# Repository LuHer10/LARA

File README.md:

# LARA (Low-cost Assistive Robot Arm)
Repositorio Trabajo Fin de Grado

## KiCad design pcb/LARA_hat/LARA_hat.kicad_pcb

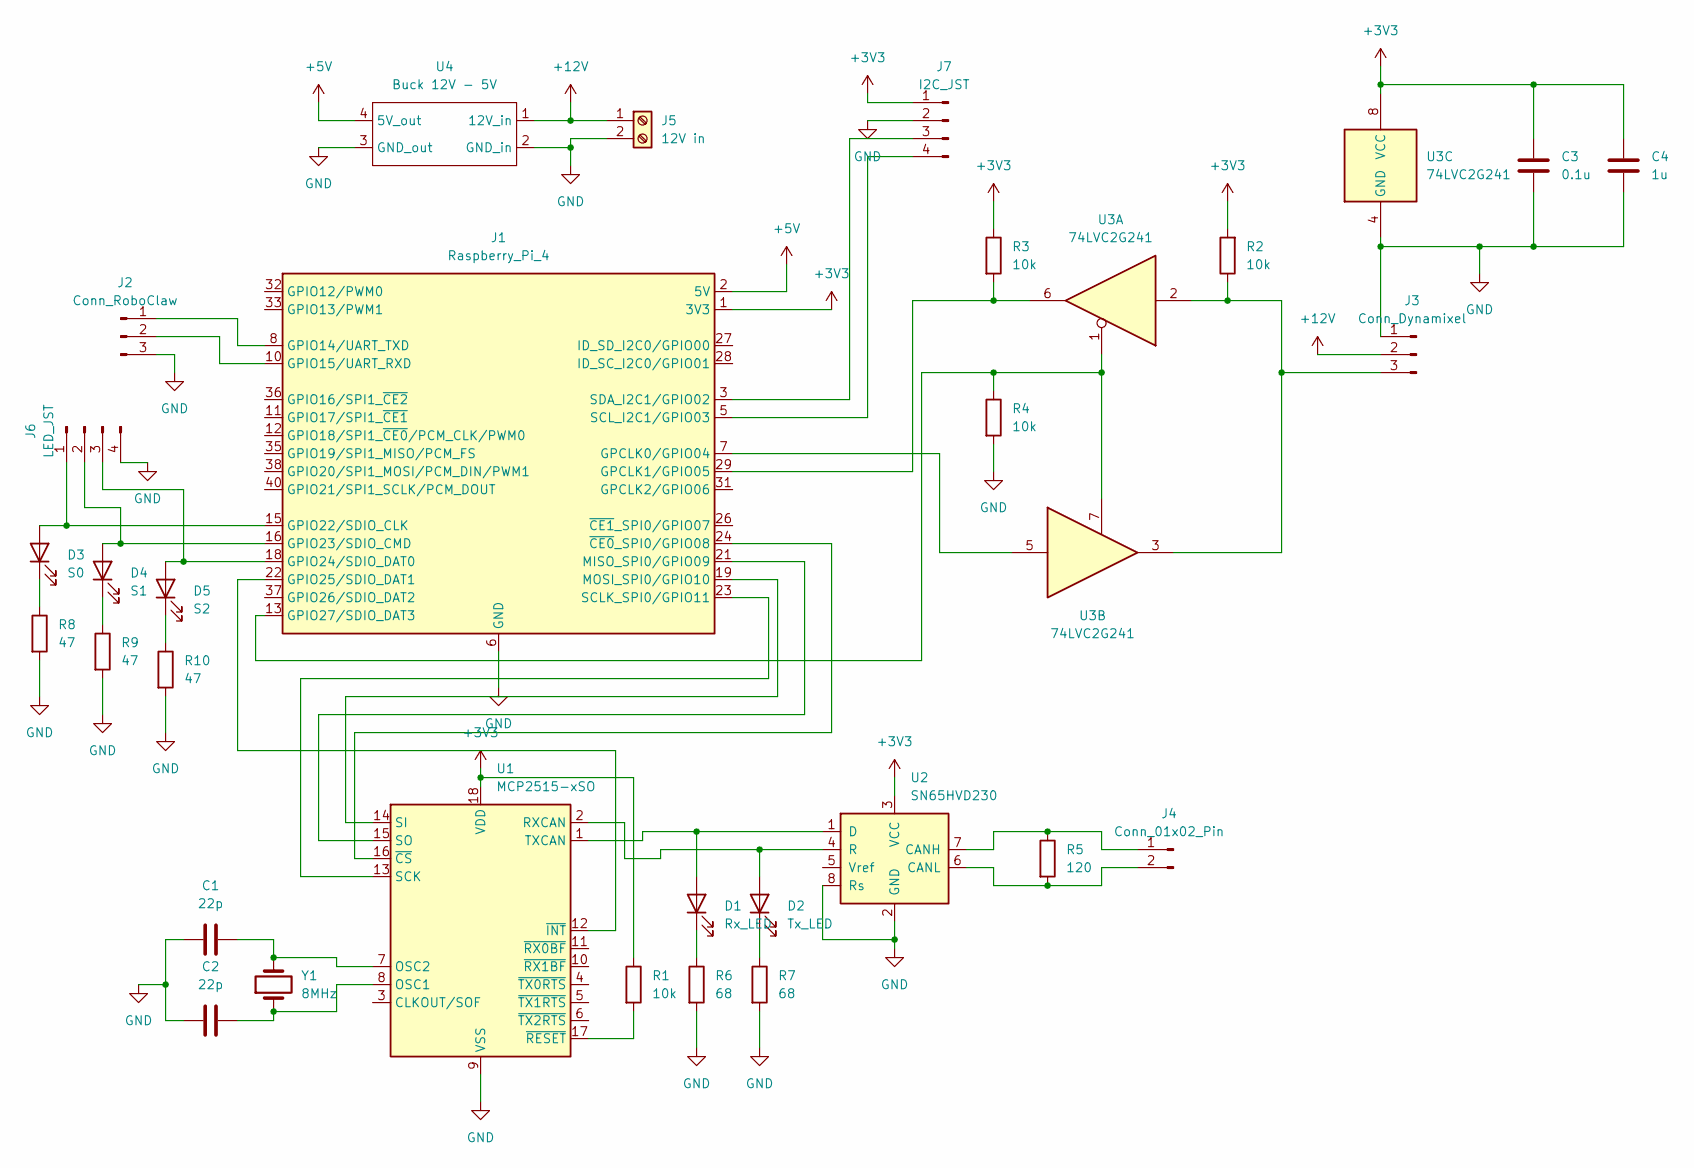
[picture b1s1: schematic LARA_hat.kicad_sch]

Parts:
C1, C2: 22p; C_0805_2012Metric_Pad1.18x1.45mm_HandSolder
C3: 0.1u; C_0805_2012Metric_Pad1.18x1.45mm_HandSolder
C4: 1u; C_0805_2012Metric_Pad1.18x1.45mm_HandSolder
D1: Rx_LED; LED_0805_2012Metric_Pad1.15x1.40mm_HandSolder
D2: Tx_LED; LED_0805_2012Metric_Pad1.15x1.40mm_HandSolder
D3: S0; LED_0805_2012Metric_Pad1.15x1.40mm_HandSolder
D4: S1; LED_0805_2012Metric_Pad1.15x1.40mm_HandSolder
D5: S2; LED_0805_2012Metric_Pad1.15x1.40mm_HandSolder
J1: Raspberry_Pi_4; PinHeader_2x20_P2.54mm_Vertical
J2: Conn_RoboClaw; JST_PH_B3B-PH-K_1x03_P2.00mm_Vertical
J3: Conn_Dynamixel; JST_EH_B3B-EH-A_1x03_P2.50mm_Vertical
J4: Conn_01x02_Pin; JST_PH_B2B-PH-K_1x02_P2.00mm_Vertical
J5: 12V in; TerminalBlock_MaiXu_MX126-5.0-02P_1x02_P5.00mm
J6: LED_JST; JST_PH_B4B-PH-K_1x04_P2.00mm_Vertical
J7: I2C_JST; JST_PH_B4B-PH-K_1x04_P2.00mm_Vertical
R1, R2, R3, R4: 10k; R_0805_2012Metric_Pad1.20x1.40mm_HandSolder
R5: 120; R_0805_2012Metric_Pad1.20x1.40mm_HandSolder
R6, R7: 68; R_0805_2012Metric_Pad1.20x1.40mm_HandSolder
R8, R9, R10: 47; R_0805_2012Metric_Pad1.20x1.40mm_HandSolder
U1: MCP2515-xSO; SOIC-18W_7.5x11.6mm_P1.27mm
U2: SN65HVD230; SOIC-8_3.9x4.9mm_P1.27mm
U3: 74LVC2G241; VSSOP-8_3x3mm_P0.65mm
U4: Buck 12V - 5V; BUCK12-5
Y1: 8MHz; Crystal_HC49-4H_Vertical

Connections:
+3V3: C3.1, C4.1, J1.1 (3V3), J1.17 (3V3), J7.1, R1.1, R2.2, R3.1, U1.18 (VDD), U2.3 (VCC), U3.8 (VCC)
+5V: J1.2 (5V), J1.4 (5V), U4.4 (5V_out)
+12V: J3.2, J5.1, U4.1 (12V_in)
GND: C1.1, C2.1, C3.2, C4.2, J1.6 (GND), J1.9 (GND), J1.14 (GND), J1.20 (GND), J1.25 (GND), J1.30 (GND), J1.34 (GND), J1.39 (GND), J2.3, J3.1, J5.2, J6.4, J7.2, R4.2, R6.2, R7.2, R8.2, R9.2, R10.2, U1.9 (VSS), U2.2 (GND), U2.8 (Rs), U3.4 (GND), U4.2 (GND_in), U4.3 (GND_out)
unnamed: D1.2 (A), U1.1 (TXCAN), U2.1 (D)
unnamed: D1.1 (K), R6.1
unnamed: D2.2 (A), U1.2 (RXCAN), U2.4 (R)
unnamed: D2.1 (K), R7.1
unnamed: D3.2 (A), J1.15 (GPIO22/SDIO_CLK), J6.1
unnamed: D3.1 (K), R8.1
unnamed: D4.2 (A), J1.16 (GPIO23/SDIO_CMD), J6.2
unnamed: D4.1 (K), R9.1
unnamed: D5.2 (A), J1.18 (GPIO24/SDIO_DAT0), J6.3
unnamed: D5.1 (K), R10.1
unnamed: J1.7 (GPCLK0/GPIO04), U3.5
unnamed: J1.29 (GPCLK1/GPIO05), R3.2, U3.6
unnamed: J1.8 (GPIO14/UART_TXD), J2.1
unnamed: J1.10 (GPIO15/UART_RXD), J2.2
unnamed: J1.22 (GPIO25/SDIO_DAT1), U1.12 (~INT)
unnamed: J1.13 (GPIO27/SDIO_DAT3), R4.1, U3.1, U3.7
unnamed: J1.21 (MISO_SPI0/GPIO09), U1.15 (SO)
unnamed: J1.19 (MOSI_SPI0/GPIO10), U1.14 (SI)
unnamed: J1.23 (SCLK_SPI0/GPIO11), U1.13 (SCK)
unnamed: J1.5 (SCL_I2C1/GPIO03), J7.4
unnamed: J1.3 (SDA_I2C1/GPIO02), J7.3
unnamed: J1.24 (~CE0_SPI0/GPIO08), U1.16 (~CS)
unnamed: J3.3, R2.1, U3.2, U3.3
unnamed: J4.1, R5.1, U2.7 (CANH)
unnamed: J4.2, R5.2, U2.6 (CANL)
unnamed: C2.2, U1.8 (OSC1), Y1.1
unnamed: C1.2, U1.7 (OSC2), Y1.2
unnamed: R1.2, U1.17 (~RESET)

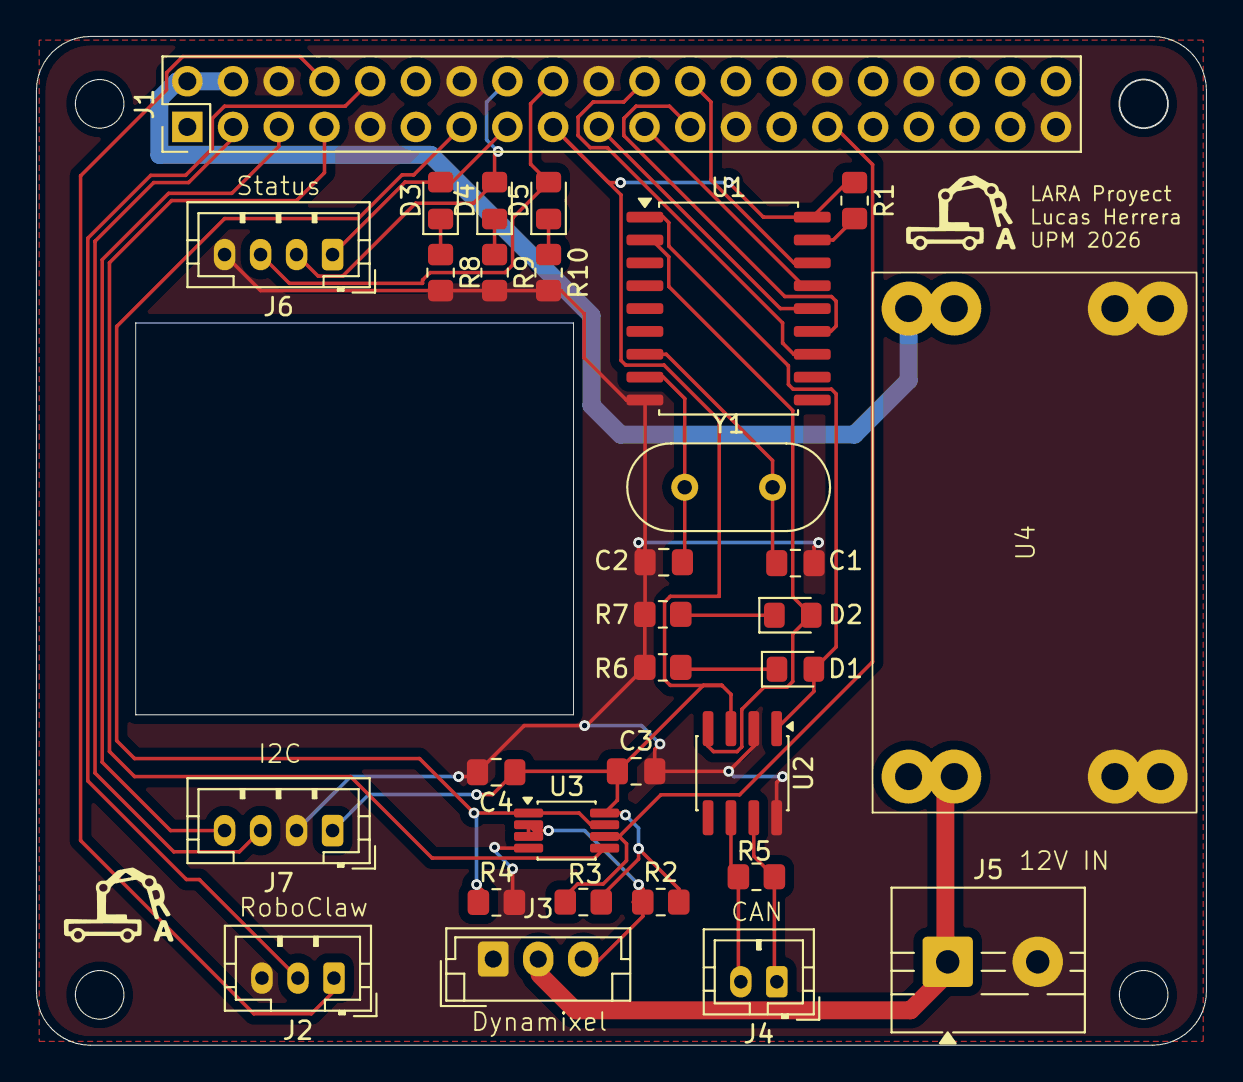
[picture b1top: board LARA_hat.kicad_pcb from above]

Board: 2 copper layers, 64.9 x 56.0 mm, 31 parts (0 on the bottom side), 32 nets.

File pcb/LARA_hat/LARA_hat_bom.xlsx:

Reference | Qty | Value | Footprint
C1,C2 | 2 | 22p | Capacitor_SMD:C_0805_2012
C3 | 1 | 0.1u | Capacitor_SMD:C_0805_2012
C4 | 1 | 1u | Capacitor_SMD:C_0805_2012
D1 | 1 | Rx_LED | LED_SMD:LED_0805_2012
D2 | 1 | Tx_LED | LED_SMD:LED_0805_2012
D3 | 1 | S0 | LED_SMD:LED_0805_2012
D4 | 1 | S1 | LED_SMD:LED_0805_2012
D5 | 1 | S2 | LED_SMD:LED_0805_2012
J1 | 1 | Raspberry_Pi_4 | Connector_PinSocket_2.54mm:PinSocket_2x20_P2.54mm_Vertical
J2 | 1 | Conn_RoboClaw | Connector_JST:JST_PH_B3B-PH-K_1x03_P2.00mm_Vertical
J3 | 1 | Conn_Dynamixel | Connector_JST:JST_EH_B3B-EH-A_1x03_P2.50mm_Vertical
J4 | 1 | Conn_01x02_Pin | Connector_JST:JST_PH_B2B-PH-K_1x02_P2.00mm_Vertical
J5 | 1 | 12V in | TerminalBlock:TerminalBlock_MaiXu_MX126-5.0-02P_1x02_P5.00mm
J6 | 1 | LED_JST | Connector_JST:JST_PH_B4B-PH-K_1x04_P2.00mm_Vertical
J7 | 1 | I2C_JST | Connector_JST:JST_PH_B4B-PH-K_1x04_P2.00mm_Vertical
R1,R2,R3,R4 | 4 | 10k | Resistor_SMD:R_0805_2012
R5 | 1 | 120 | Resistor_SMD:R_0805_2012
R6,R7,R8,R9,R10 | 5 | 68 | Resistor_SMD:R_0805_2012
U1 | 1 | MCP2515-xSO | Package_SO:SOIC-18W_7.5x11.6mm_P1.27mm
U2 | 1 | SN65HVD230 | Package_SO:SOIC-8_3.9x4.9mm_P1.27mm
U3 | 1 | 74LVC2G241 | Package_SO:VSSOP-8_3x3mm_P0.65mm
Y1 | 1 | 8MHz | Crystal:Crystal_HC49-4H_Vertical

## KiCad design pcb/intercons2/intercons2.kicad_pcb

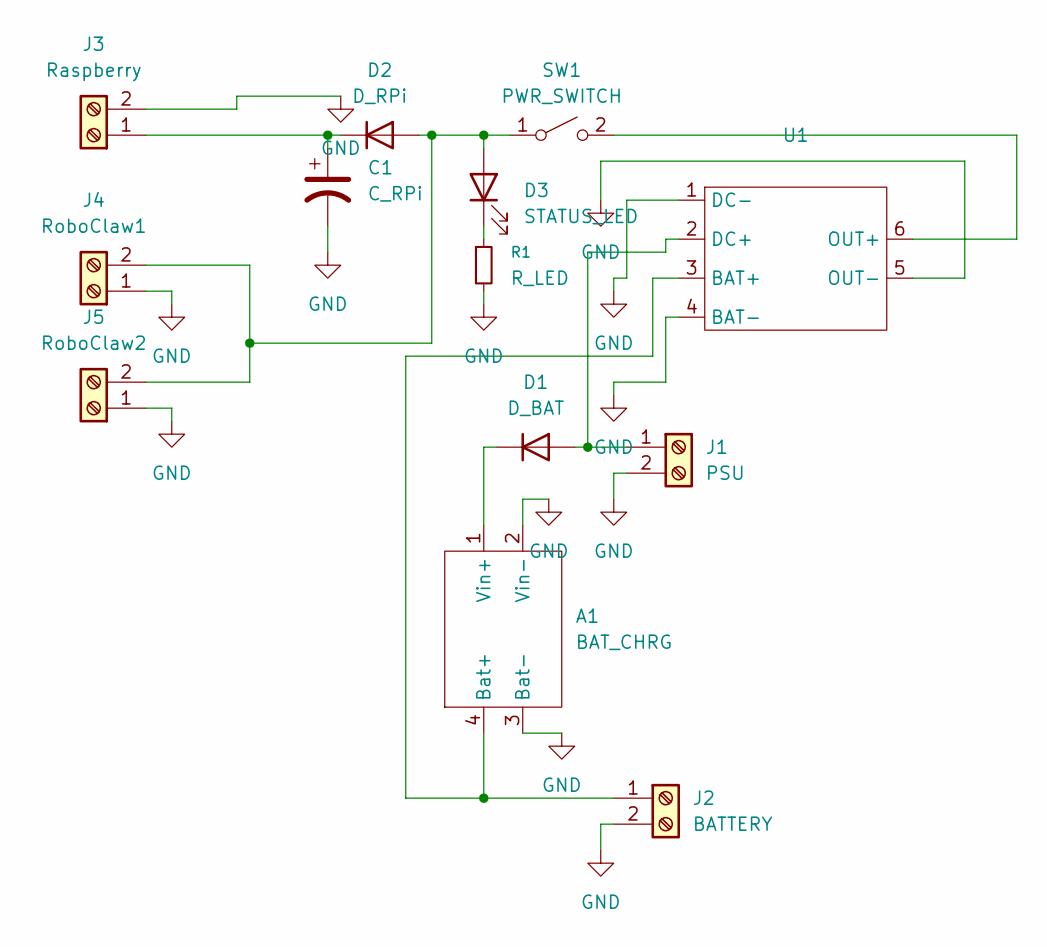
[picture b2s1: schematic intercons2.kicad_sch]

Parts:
A1: BAT_CHRG
C1: C_RPi; CP_Radial_D18.0mm_P7.50mm
D1: D_BAT; D_DO-27_P15.24mm_Horizontal
D2: D_RPi; D_DO-27_P15.24mm_Horizontal
D3: STATUS_LED; LED_D3.0mm
J1: PSU; TerminalBlock_MaiXu_MX126-5.0-02P_1x02_P5.00mm
J2: BATTERY; TerminalBlock_MaiXu_MX126-5.0-02P_1x02_P5.00mm
J3: Raspberry; TerminalBlock_MaiXu_MX126-5.0-02P_1x02_P5.00mm
J4: RoboClaw1; TerminalBlock_MaiXu_MX126-5.0-02P_1x02_P5.00mm
J5: RoboClaw2; TerminalBlock_MaiXu_MX126-5.0-02P_1x02_P5.00mm
R1: R_LED; R_Axial_DIN0204_L3.6mm_D1.6mm_P7.62mm_Horizontal
SW1: PWR_SWITCH; switch
U1: COMMUTER

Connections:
GND: A1.2 (Vin-), A1.3 (Bat-), C1.2, J1.2, J2.2, J3.2, J4.1, J5.1, R1.2, U1.1 (DC-), U1.4 (BAT-), U1.5 (OUT-)
unnamed: A1.4 (Bat+), J2.1, U1.3 (BAT+)
unnamed: A1.1 (Vin+), D1.1 (K)
unnamed: D1.2 (A), J1.1, U1.2 (DC+)
unnamed: D2.2 (A), D3.2 (A), J4.2, J5.2, SW1.1 (A)
unnamed: C1.1, D2.1 (K), J3.1
unnamed: D3.1 (K), R1.1
unnamed: SW1.2 (B), U1.6 (OUT+)

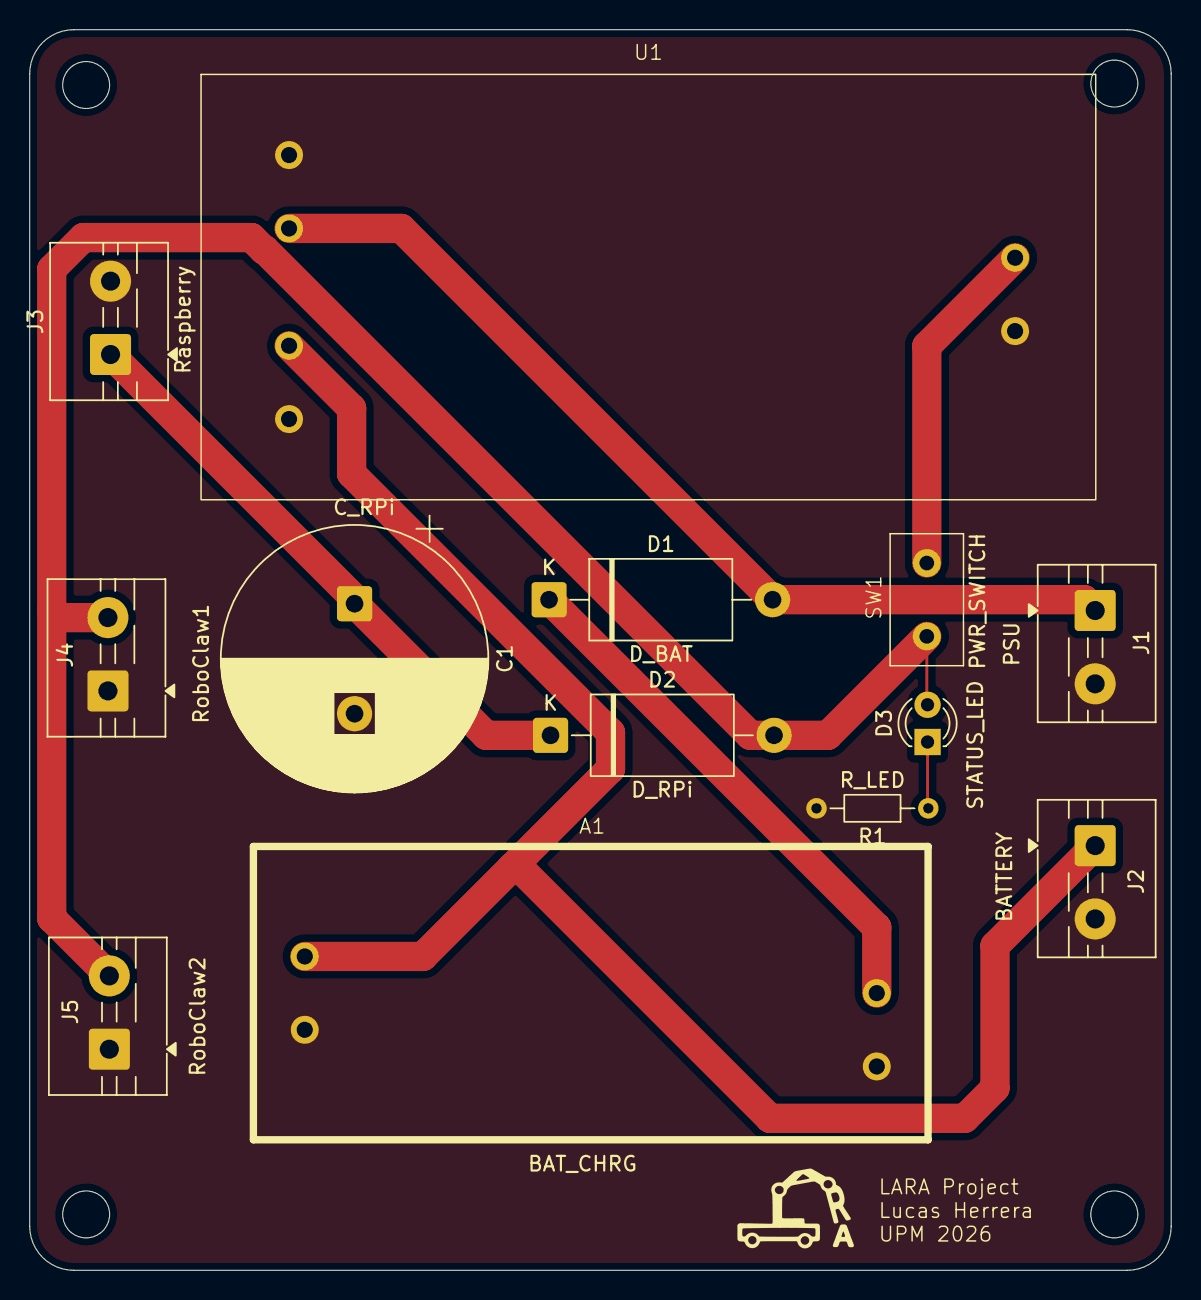
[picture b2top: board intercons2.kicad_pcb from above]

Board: 2 copper layers, 77.8 x 84.6 mm, 15 parts (1 on the bottom side), 8 nets.

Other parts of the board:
logo1, logo3: LOGO

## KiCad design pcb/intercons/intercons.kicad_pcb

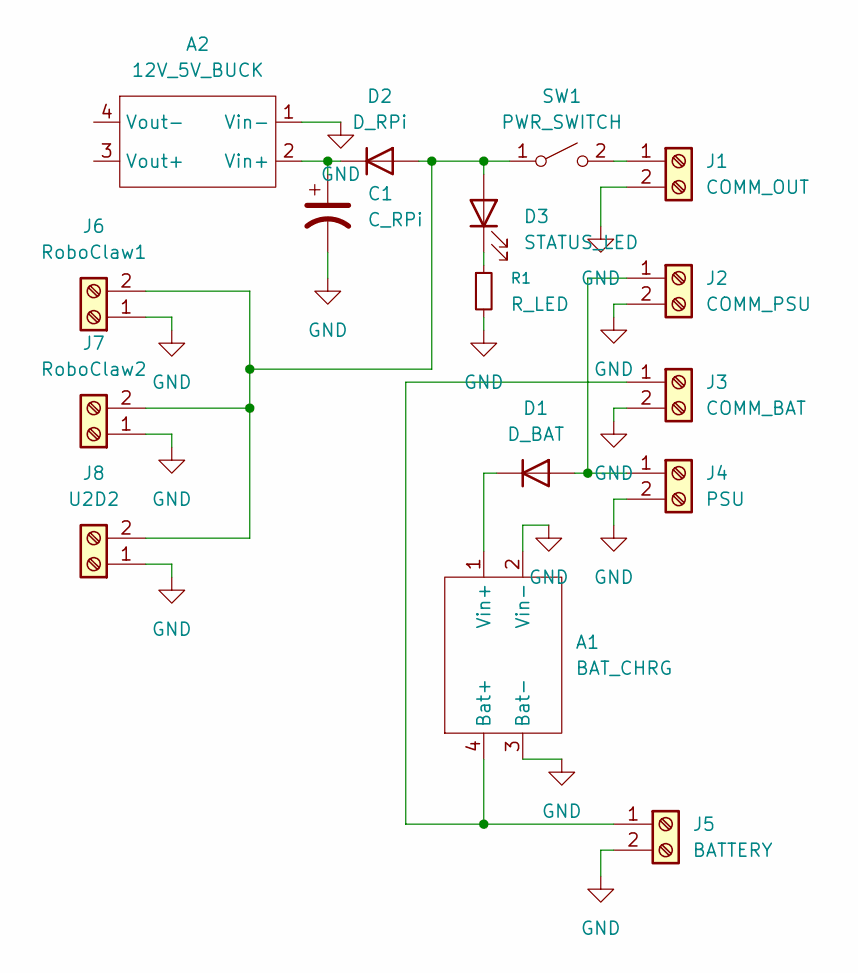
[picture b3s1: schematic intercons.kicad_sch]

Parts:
A1: BAT_CHRG
A2: 12V_5V_BUCK
C1: C_RPi; CP_Radial_D18.0mm_P7.50mm
D1: D_BAT; D_DO-27_P15.24mm_Horizontal
D2: D_RPi; D_DO-27_P15.24mm_Horizontal
D3: STATUS_LED; LED_D3.0mm
J1: COMM_OUT; TerminalBlock_MaiXu_MX126-5.0-02P_1x02_P5.00mm
J2: COMM_PSU; TerminalBlock_MaiXu_MX126-5.0-02P_1x02_P5.00mm
J3: COMM_BAT; TerminalBlock_MaiXu_MX126-5.0-02P_1x02_P5.00mm
J4: PSU; TerminalBlock_MaiXu_MX126-5.0-02P_1x02_P5.00mm
J5: BATTERY; TerminalBlock_MaiXu_MX126-5.0-02P_1x02_P5.00mm
J6: RoboClaw1; TerminalBlock_MaiXu_MX126-5.0-02P_1x02_P5.00mm
J7: RoboClaw2; TerminalBlock_MaiXu_MX126-5.0-02P_1x02_P5.00mm
J8: U2D2; TerminalBlock_MaiXu_MX126-5.0-02P_1x02_P5.00mm
R1: R_LED; R_Axial_DIN0204_L3.6mm_D1.6mm_P7.62mm_Horizontal
SW1: PWR_SWITCH; switch

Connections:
GND: A1.2 (Vin-), A1.3 (Bat-), A2.1 (Vin-), C1.2, J1.2, J2.2, J3.2, J4.2, J5.2, J6.1, J7.1, J8.1, R1.2
unnamed: A1.4 (Bat+), J3.1, J5.1
unnamed: A1.1 (Vin+), D1.1 (K)
unnamed: A2.2 (Vin+), C1.1, D2.1 (K)
unnamed: D1.2 (A), J2.1, J4.1
unnamed: D2.2 (A), D3.2 (A), J6.2, J7.2, J8.2, SW1.1 (A)
unnamed: D3.1 (K), R1.1
unnamed: J1.1, SW1.2 (B)

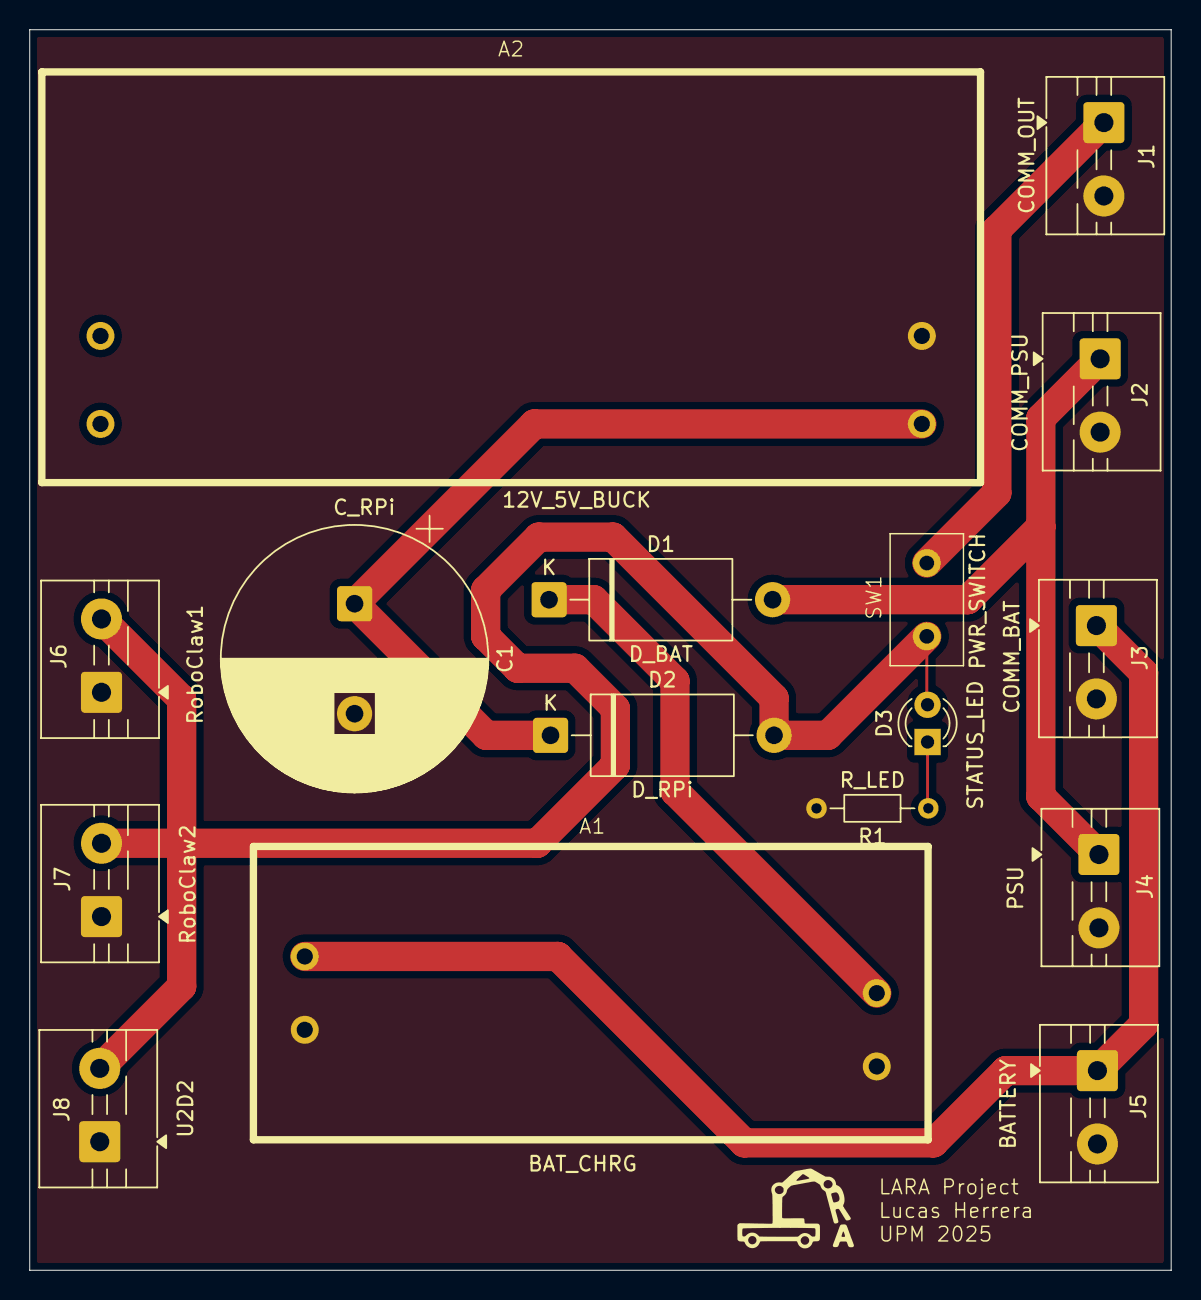
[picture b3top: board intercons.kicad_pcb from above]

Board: 2 copper layers, 77.8 x 84.6 mm, 18 parts (1 on the bottom side), 8 nets.

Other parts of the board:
logo1, logo3: LOGO

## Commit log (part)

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2025-06-08 test
2025-06-08 robot main.cpp added
2025-06-09 modified roboclaw_test program
2025-06-09 added Qt app code
2025-06-10 default RPi baud rate 115200
2025-06-13 added roboclaw.h to robot folder
2025-06-13 added roboclaw.cpp to robot folder
2025-06-13 modified main.cpp in robot to use roboclaw library
2025-06-13 new file structure
2025-06-14 added .gitignore
2025-06-14 added CMakelists.txt to robot
2025-06-14 CC BY-NC-SA 4.0 license
2025-06-15 updated .gitignore
2025-06-15 added functions for PWM and speed commands
2025-06-16 added encoder read method
2025-06-17 fixed error: bad file descriptor
2025-06-18 fixed encoder misread
2025-06-18 added encoder reset method
2025-06-18 added reaad speed method
2025-06-18 added base.h and base.cpp (Base class)
2025-06-19 added odometry functions to Base
2025-06-20 changed CMake structure
2025-06-20 changed test folder structure (CMake)
2025-06-23 Added destructor to base (stops the motors)
2025-06-23 added readSpeeds()
2025-06-23 added udp test program
2025-06-23 updated qt_app
2025-06-24 added test program for Base class
2025-06-24 updated CMakeLists.txt
2025-06-24 added test program for udp motor control
2025-06-24 fixed errors
2025-06-24 updated base.cpp
2025-06-24 updated udp_motor.cpp
2025-06-25 added new Network class
2025-06-25 added test program for network class
2025-06-25 updated base dimensions
2025-06-26 changed qt_app file structure
2025-06-26 added JoystickApp test project
2025-06-27 changed GUI in JoystickApp
2025-07-02 updated JoystickApp
2025-07-02 added designs folder
2025-07-07 added upper arm segments
2025-07-08 Updated servo placements for belts
2025-07-08 added gt2 belt calculator
2025-07-08 added pulley designs
2025-07-08 added pulley design
2025-07-15 changed pulleys to 25T - 50T
2025-07-15 updated pulleys
2025-07-15 new pulleys
2025-07-15 update AndroidManifest
2025-07-15 updated udp_motor_network.cpp
2025-07-22 changed belt lengths
2025-07-23 made holes for spacers
2025-07-23 24T and 48T pulleys
2025-07-24 improved message send/receive
2025-09-03 added arm assembly
2025-09-09 updated arm assembly
2025-09-16 dxf files added
2025-09-16 added new FCStd files
2025-09-17 updated pulley
2025-09-23 added bearing cover designs
2025-10-06 added spacers
2025-10-06 Updated external cover
2025-10-06 Updated covers
2025-10-17 updated gt2 48T pulley
2025-10-17 new covers
2025-10-21 changed server IP address
2025-10-23 updated/added parts
2025-10-23 increased inner diameter to 6mm
2025-10-27 added 0.2mm clearance
2025-10-28 pulleys optimized for printing
2025-10-28 spiky gt2 pulley generator
2025-10-30 added base designs
2025-11-14 added wrist
2025-11-14 fixed pulley
2025-11-14 new spacers
2025-11-14 pieces
2025-11-24 added KiCAD files
2025-11-28 new arm version
2025-12-01 added 6mm to servo slot
2025-12-02 added servo class
2025-12-02 added angle to position converter functions
2025-12-04 added operating mode functions
2025-12-04 fixed inverse kinematics error
2025-12-09 added arm attachment to base
2025-12-09 updated arm_base
2026-01-08 error fix
2026-01-08 added arm classs
2026-01-09 added grip button
2026-01-09 fixed error
2026-01-09 added out of reach detection
2026-01-09 arm test program
2026-01-12 updated base
2026-01-13 updated hole distance
2026-01-13 added gripper folder and files
2026-01-14 updated CMakeLists.txt for dynamixel_sdk for x64
2026-01-14 updated servo.h
2026-01-14 added test programs
2026-01-14 updated arm library
2026-01-14 corrected width
2026-01-14 fixed error in kinematics
2026-01-15 new parts
2026-01-17 added kinematics function with output variables
2026-01-17 general improvement
2026-01-17 updated arm test program
2026-01-20 added deadzone to joysticks
2026-01-20 test done
2026-01-21 sends data to servos when joystick values non-zero
2026-01-21 added macros for servo IDs
2026-01-23 new button for manual arm control
2026-01-25 added gripper piece
2026-01-26 odometry test
2026-01-27 added odometry test programs
2026-01-27 odometry tests
2026-01-30 it works
2026-02-01 added stl files
2026-03-11 new pcb hat
2026-03-16 pcb update
2026-04-08 replaced wrong intercons pcb files
2026-04-08 pcb gerbers
2026-04-14 new intercons2 pcb
2026-04-15 bom update
2026-04-17 pcb upddates + gerbers
2026-05-21 pcb error fixed
